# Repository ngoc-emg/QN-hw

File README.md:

# QN-hw
hardware platform arduino 2560

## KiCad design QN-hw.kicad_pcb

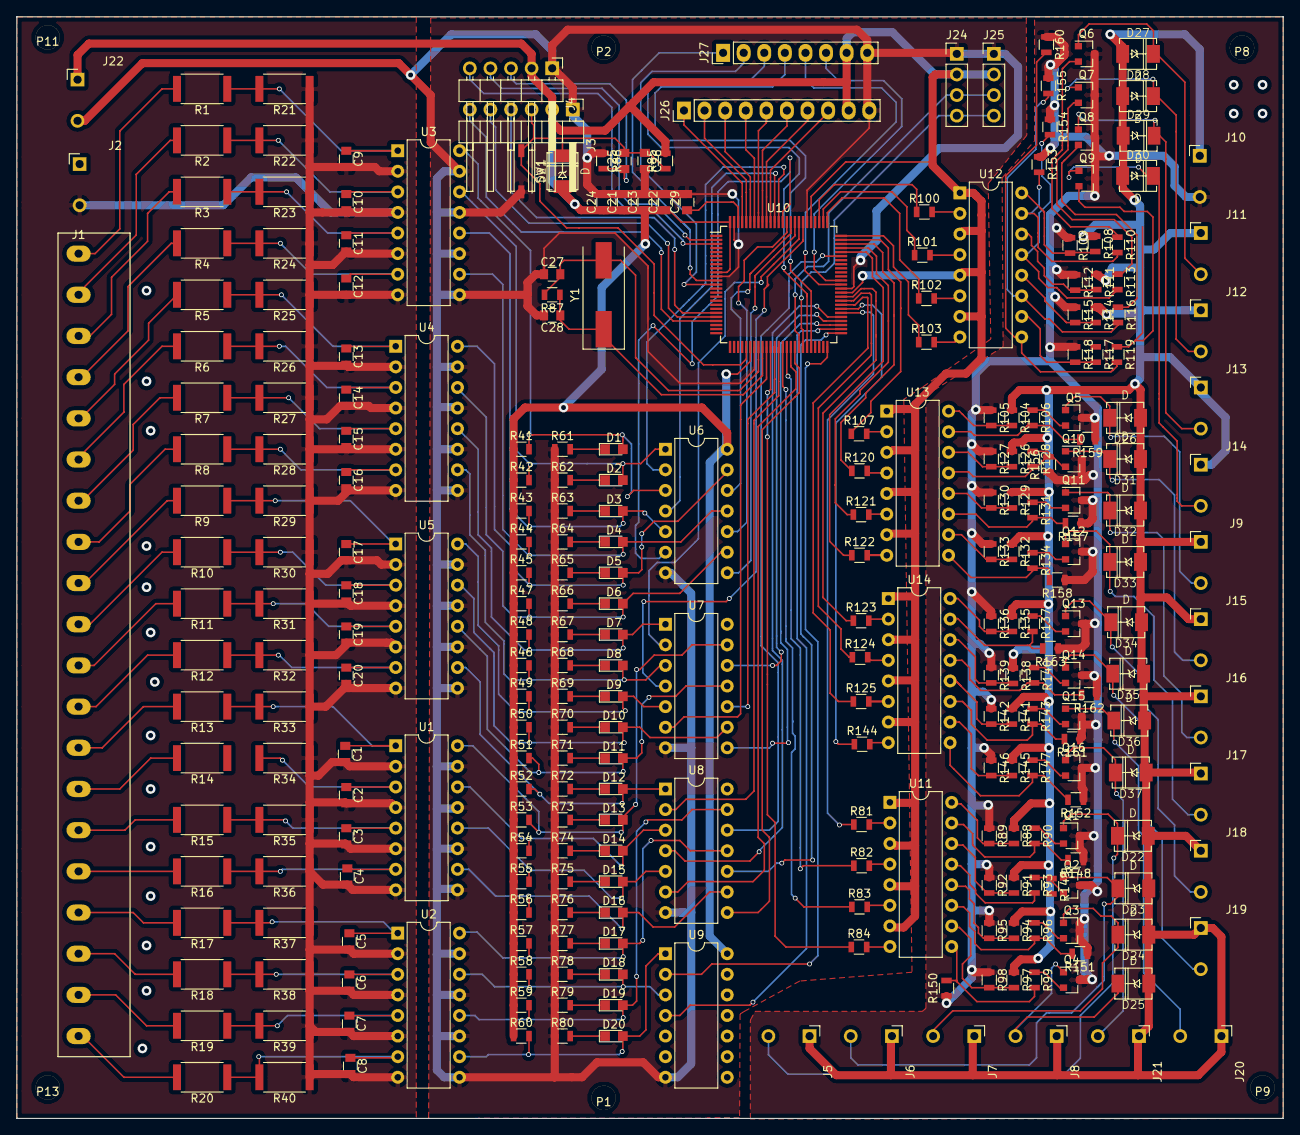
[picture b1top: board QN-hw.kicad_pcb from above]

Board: 2 copper layers, 156.2 x 135.9 mm, 293 parts (0 on the bottom side), 227 nets.

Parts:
C1, C2, C3, C4, C5, C6, C7, C8, C9, C10, C11, C12, C13, C14, C15, C16, C17, C18, C19, C20: 1uF; C_0805
C21, C22, C23, C24, C25, C29: 0.1uF; C_0805
C26, C27, C28: 22pF; C_0805
D1, D2, D3, D4, D5, D6, D7, D8, D9, D10, D11, D12, D13, D14, D15, D16, D17, D18, D19, D20: LED; LED_0805
D21, D22, D23, D24, D25, D26, D27, D28, D29, D30, D31, D32, D33, D34, D35, D36, D37: D; DO-214AC(SMA)
J1: Conn_01x20; Terminal-block-20
J2, J10: +24V; Pin_Header_Angled_1x02_Pitch2.54mm
J3: Boot -loader; Pin_Header_Angled_1x06_Pitch2.54mm
J4: Nap-CT; Pin_Header_Angled_1x05_Pitch2.54mm
J5, J6, J7, J8, J9, J11, J12, J13, J14, J15, J16, J17, J18, J19, J20, J21: Conn_01x02; Pin_Header_Angled_1x02_Pitch2.54mm
J22: +5V; Pin_Header_Angled_1x02_Pitch2.54mm
J24, J25: I2C; Pin_Header_Straight_1x04_Pitch2.54mm
J26: ADC-5V; Pin_Header_Straight_1x10_Pitch2.54mm
J27: UART; Pin_Header_Straight_1x08_Pitch2.54mm
P1, P2, P8, P9, P11, P13: CONN_01X01; Vit-3mm
Q1, Q2, Q3, Q4, Q5, Q6, Q7, Q8, Q9, Q10, Q11, Q12, Q13, Q14, Q15, Q16: Q_NMOS_DGS; SOT-23
R1, R2, R3, R4, R5, R6, R7, R8, R9, R10, R11, R12, R13, R14, R15, R16, R17, R18, R19, R20: 3K3/0.6W; R_2512
R21, R22, R23, R24, R25, R26, R27, R28, R29, R30, R31, R32, R33, R34, R35, R36, R37, R38, R39, R40: 1K/0.6W; R_2512
R41, R42, R43, R44, R45, R46, R47, R48, R49, R50, R51, R52, R53, R54, R55, R56, R57, R58, R59, R60, R85, R104, R159: 10K; R_0805
R61, R62, R63, R64, R65, R66, R67, R68, R69, R70, R71, R72, R73, R74, R75, R76, R77, R78, R79, R80, R81, R82, R83, R84, R100, R101, R102, R103, R107, R120, R121, R122, R123, R124, R125, R144: 220R; R_0805
R86, R105: 1K; R_0805
R87: 1M; R_0805
R88, R91, R94, R97, R108, R111, R114, R117, R126, R129, R132, R135, R138, R141, R145, R148, R149, R150, R151, R152, R153, R154, R155, R156, R157, R158, R160, R161, R162, R163: 10K/0.6W; R_0805
R89, R92, R95, R98, R109, R112, R115, R118, R127, R130, R133, R136, R139, R142, R146: 1K/0.6W; R_0805
R90, R93, R96, R99, R110, R113, R116, R119, R128, R131, R134, R137, R140, R143: 10R/0.6W; R_0805
R106: 10R; R_0805
R147: 10/R0.6W; R_0805
SW1: SW_Push; SW_DIP_x1_W5.08mm_Slide_Copal_CHS-A
U1, U2, U3, U4, U5, U11, U12, U13, U14: TLP627-4; DIP-16_W7.62mm
U6, U7, U8, U9: 74HC14; DIP-14_W7.62mm
U10: ATMEGA2560-16AU; TQFP-100_14x14mm_Pitch0.5mm
Y1: 20Mhz; Crystal_SMD_HC49-SD

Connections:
22: R100.1, U10.78
23: R101.1, U10.77
24: R102.1, U10.76
25: R103.1, U10.75
26: R107.1, U10.74
27: R120.1, U10.73
28: R121.1, U10.72
29: R122.1, U10.71
30: R123.1, U10.60
31: R124.1, U10.59
32: R125.1, U10.58
33: R144.1, U10.57
34: R81.1, U10.56
35: U8.4, U10.55
36: U7.12, U10.54
37: U7.8, U10.53
38: U9.2, U10.50
39: U8.12, U10.70
40: U9.4, U10.52
41: U8.10, U10.51
42: U8.8, U10.42
43: U8.6, U10.41
44: R82.1, U10.40
45: R83.1, U10.39
46: U8.2, U10.38
47: U7.10, U10.37
48: R84.1, U10.36
49: U7.6, U10.35
/0V-IN: C1.2, C2.2, C3.2, C4.2, C5.2, C6.2, C7.2, C8.2, C9.2, C10.2, C11.2, C12.2, C13.2, C14.2, C15.2, C16.2, C17.2, C18.2, C19.2, C20.2, J2.2, R21.1, R22.1, R23.1, R24.1, R25.1, R26.1, R27.1, R28.1, R29.1, R30.1, R31.1, R32.1, R33.1, R34.1, R35.1, R36.1, R37.1, R38.1, R39.1, R40.1, U1.2, U1.4, U1.6, U1.8, U2.2, U2.4, U2.6, U2.8, U3.2, U3.4, U3.6, U3.8, U4.2, U4.4, U4.6, U4.8, U5.2, U5.4, U5.6, U5.8
/0V-OUT: J10.2, Q1.3, Q2.3, Q3.3, Q4.3, Q5.3, Q6.3, Q7.3, Q8.3, Q9.3, Q10.3, Q11.3, Q12.3, Q13.3, Q14.3, Q15.3, Q16.3, R89.1, R92.1, R95.1, R98.1, R105.1, R109.1, R112.1, R115.1, R118.1, R127.1, R130.1, R133.1, R136.1, R139.1, R142.1, R146.1, R148.1, R149.1, R150.1, R151.1, R152.1, R153.1, R154.1, R155.1, R156.1, R157.1, R158.1, R159.1, R160.1, R161.1, R162.1, R163.1
/+24V-OUT: D22.1, D23.1, D24.1, D25.1, D26.1, D27.1, D28.1, D29.1, D30.1, D31.1, D32.1, D33.1, D34.1, D35.1, D36.1, D37.1, J5.1, J6.1, J7.1, J8.1, J9.1, J10.1, J11.1, J12.1, J13.1, J14.1, J15.1, J16.1, J17.1, J18.1, J19.1, J20.1, J21.1, R88.1, R91.1, R94.1, R97.1, R104.1, R108.1, R111.1, R114.1, R117.1, R126.1, R129.1, R132.1, R135.1, R138.1, R141.1, R145.1
/IN1: J1.1, R1.2
/IN2: J1.2, R2.2
/IN3: J1.3, R3.2
/IN4: J1.4, R4.2
/IN5: J1.5, R5.2
/IN6: J1.6, R6.2
/IN7: J1.7, R7.2
/IN8: J1.8, R8.2
/IN9: J1.9, R9.2
/IN10: J1.10, R10.2
/IN11: J1.11, R11.2
/IN12: J1.12, R12.2
/IN13: J1.13, R13.2
/IN14: J1.14, R14.2
/IN15: J1.15, R15.2
/IN16: J1.16, R16.2
/IN17: J1.17, R17.2
/IN18: J1.18, R18.2
/IN19: J1.19, R19.2
/IN20: J1.20, R20.2
A0: J26.1, U10.97
A1: J26.2, U10.96
A2: J26.3, U10.95
A3: J26.4, U10.94
A4: J26.5, U10.93
A5: J26.6, U10.92
A6: J26.7, U10.91
A7: J26.8, U10.90
A8: U6.4, U10.89
A9: U6.2, U10.88
A10: U6.6, U10.87
A11: U6.10, U10.86
A12: U6.12, U10.85
A13: U6.8, U10.84
A14: U7.2, U10.83
A15: U7.4, U10.82
DTR: C25.1, J4.3, R86.2
GND: C21.2, C22.2, C23.2, C24.2, C26.2, C27.1, C28.2, C29.2, J3.1, J4.1, J22.2, J24.1, J25.1, J26.10, J27.8, R61.1, R62.1, R63.1, R64.1, R65.1, R66.1, R67.1, R68.1, R69.1, R70.1, R71.1, R72.1, R73.1, R74.1, R75.1, R76.1, R77.1, R78.1, R79.1, R80.1, R86.1, SW1.2, U1.9, U1.11, U1.13, U1.15, U2.9, U2.11, U2.13, U2.15, U3.9, U3.11, U3.13, U3.15, U4.9, U4.11, U4.13, U4.15, U5.9, U5.11, U5.13, U5.15, U6.7, U7.7, U8.7, U9.7, U10.11, U10.32, U10.62, U10.81, U10.99
I1: D1.2, R41.2, U3.16, U6.3
I2: D2.2, R42.2, U3.14, U6.1
I3: D3.2, R43.2, U3.12, U6.5
I4: D4.2, R44.2, U3.10, U6.11
I5: D5.2, R45.2, U4.16, U6.13
I6: D6.2, R47.2, U4.14, U6.9
I7: D7.2, R48.2, U4.12, U7.1
I8: D8.2, R46.2, U4.10, U7.3
I9: D9.2, R49.2, U5.16, U7.5
I10: D10.2, R50.2, U5.14, U7.9
I11: D11.2, R51.2, U5.12, U7.11
I12: D12.2, R52.2, U5.10, U8.1
I13: D13.2, R53.2, U1.16, U7.13
I14: D14.2, R54.2, U1.14, U8.3
I15: D15.2, R55.2, U1.12, U8.5
I16: D16.2, R56.2, U1.10, U8.9
I17: D17.2, R57.2, U2.16, U8.11
I18: D18.2, R58.2, U2.14, U9.3
I19: D19.2, R59.2, U2.12, U8.13
I20: D20.2, R60.2, U2.10, U9.1
MISO: J3.6, U10.22
MOSI: J3.5, U10.21
unnamed: C1.1, R13.1, R33.2, U1.1
unnamed: C2.1, R14.1, R34.2, U1.3
unnamed: C3.1, R15.1, R35.2, U1.5
unnamed: C4.1, R16.1, R36.2, U1.7
unnamed: C5.1, R17.1, R37.2, U2.1
unnamed: C6.1, R18.1, R38.2, U2.3
unnamed: C7.1, R19.1, R39.2, U2.5
unnamed: C8.1, R20.1, R40.2, U2.7
unnamed: C9.1, R1.1, R21.2, U3.1
unnamed: C10.1, R2.1, R22.2, U3.3
unnamed: C11.1, R3.1, R23.2, U3.5
unnamed: C12.1, R4.1, R24.2, U3.7
unnamed: C13.1, R5.1, R25.2, U4.1
unnamed: C14.1, R6.1, R26.2, U4.3
unnamed: C15.1, R7.1, R27.2, U4.5
unnamed: C16.1, R8.1, R28.2, U4.7
unnamed: C17.1, R9.1, R29.2, U5.1
unnamed: C18.1, R10.1, R30.2, U5.3
unnamed: C19.1, R11.1, R31.2, U5.5
unnamed: C20.1, R12.1, R32.2, U5.7
unnamed: C27.2, R87.2, U10.33, Y1.2
unnamed: C28.1, R87.1, U10.34, Y1.1
unnamed: C29.1, U10.98
unnamed: D1.1, R61.2
unnamed: D2.1, R62.2
unnamed: D3.1, R63.2
unnamed: D4.1, R64.2
unnamed: D5.1, R65.2
unnamed: D6.1, R66.2
unnamed: D7.1, R67.2
unnamed: D8.1, R68.2
unnamed: D9.1, R69.2
unnamed: D10.1, R70.2
unnamed: D11.1, R71.2
unnamed: D12.1, R72.2
unnamed: D13.1, R73.2
unnamed: D14.1, R74.2
unnamed: D15.1, R75.2
unnamed: D16.1, R76.2
unnamed: D17.1, R77.2
unnamed: D18.1, R78.2
unnamed: D19.1, R79.2
unnamed: D20.1, R80.2
unnamed: D22.2, J5.2, Q1.1
unnamed: D23.2, J6.2, Q2.1
unnamed: D24.2, J7.2, Q3.1
unnamed: D25.2, J8.2, Q4.1
unnamed: D26.2, J9.2, Q5.1
unnamed: D27.2, J11.2, Q6.1
unnamed: D28.2, J12.2, Q7.1
unnamed: D29.2, J13.2, Q8.1
unnamed: D30.2, J14.2, Q9.1
unnamed: D31.2, J15.2, Q10.1
unnamed: D32.2, J16.2, Q11.1
unnamed: D33.2, J17.2, Q12.1
unnamed: D34.2, J18.2, Q13.1
unnamed: D35.2, J19.2, Q14.1
unnamed: D36.2, J20.2, Q15.1
unnamed: D37.2, J21.2, Q16.1
unnamed: Q1.2, R90.1
unnamed: Q2.2, R93.1
unnamed: Q3.2, R96.1
unnamed: Q4.2, R99.1
unnamed: Q5.2, R106.1
unnamed: Q6.2, R110.1
unnamed: Q7.2, R113.1
unnamed: Q8.2, R116.1
unnamed: Q9.2, R119.1
unnamed: Q10.2, R128.1
unnamed: Q11.2, R131.1
unnamed: Q12.2, R134.1
unnamed: Q13.2, R137.1
unnamed: Q14.2, R140.1
unnamed: Q15.2, R143.1
unnamed: Q16.2, R147.1
unnamed: R81.2, U11.2
unnamed: R82.2, U11.4
unnamed: R83.2, U11.6
unnamed: R84.2, U11.8
unnamed: R88.2, R89.2, U11.16
unnamed: R91.2, R92.2, U11.14
unnamed: R94.2, R95.2, U11.12
unnamed: R97.2, R98.2, U11.10
unnamed: R100.2, U12.2
unnamed: R101.2, U12.4
unnamed: R102.2, U12.6
unnamed: R103.2, U12.8
unnamed: R104.2, R105.2, U13.16
unnamed: R106.2, R159.2, U13.15
unnamed: R107.2, U13.2
unnamed: R108.2, R109.2, U12.16
unnamed: R110.2, R153.2, U12.15
unnamed: R111.2, R112.2, U12.14
unnamed: R113.2, R154.2, U12.13
unnamed: R114.2, R115.2, U12.12
unnamed: R116.2, R155.2, U12.11
unnamed: R117.2, R118.2, U12.10
unnamed: R119.2, R160.2, U12.9
unnamed: R120.2, U13.4
unnamed: R121.2, U13.6
unnamed: R122.2, U13.8
unnamed: R123.2, U14.2
unnamed: R124.2, U14.4
unnamed: R125.2, U14.6
unnamed: R126.2, R127.2, U13.14
unnamed: R128.2, R156.2, U13.13
unnamed: R129.2, R130.2, U13.12
unnamed: R131.2, R157.2, U13.11
unnamed: R132.2, R133.2, U13.10
unnamed: R134.2, R158.2, U13.9
unnamed: R135.2, R136.2, U14.16
unnamed: R137.2, R163.2, U14.15
unnamed: R138.2, R139.2, U14.14
unnamed: R140.2, R162.2, U14.13
unnamed: R141.2, R142.2, U14.12
unnamed: R143.2, R161.2, U14.11
unnamed: R144.2, U14.8
unnamed: R145.2, R146.2, U14.10
unnamed: R147.2, R152.2, U14.9
unnamed: R90.2, R148.2, U11.15
unnamed: R93.2, R149.2, U11.13
unnamed: R99.2, R150.2, U11.9
unnamed: R96.2, R151.2, U11.11
RST: C25.2, C26.1, D21.2, J3.3, R85.1, SW1.1, U10.30
RX0: J4.4, U10.2
RX1: J27.3, U10.45
RX2: J27.1, U10.12
RX3: J27.5, U10.63
SCK: J3.4, U10.20
SCL: J24.3, J25.3, U10.43
SDA: J24.4, J25.4, U10.44
TX0: J4.5, U10.3
TX1: J27.4, U10.46
TX2: J27.2, U10.13
TX3: J27.6, U10.64
VCC: C21.1, C22.1, C23.1, C24.1, D21.1, J3.2, J4.2, J22.1, J24.2, J25.2, J26.9, J27.7, R41.1, R42.1, R43.1, R44.1, R45.1, R46.1, R47.1, R48.1, R49.1, R50.1, R51.1, R52.1, R53.1, R54.1, R55.1, R56.1, R57.1, R58.1, R59.1, R60.1, R85.2, U6.14, U7.14, U8.14, U9.14, U10.10, U10.31, U10.61, U10.80, U10.100, U11.1, U11.3, U11.5, U11.7, U12.1, U12.3, U12.5, U12.7, U13.1, U13.3, U13.5, U13.7, U14.1, U14.3, U14.5, U14.7

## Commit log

2018-04-02 tao project
2018-04-02 ngay-1
2018-04-03 make input
2018-04-06 input
2018-04-10 schamatic
2018-04-11 sap xep linh kien
2018-05-21 complete
2018-06-27 fix all
